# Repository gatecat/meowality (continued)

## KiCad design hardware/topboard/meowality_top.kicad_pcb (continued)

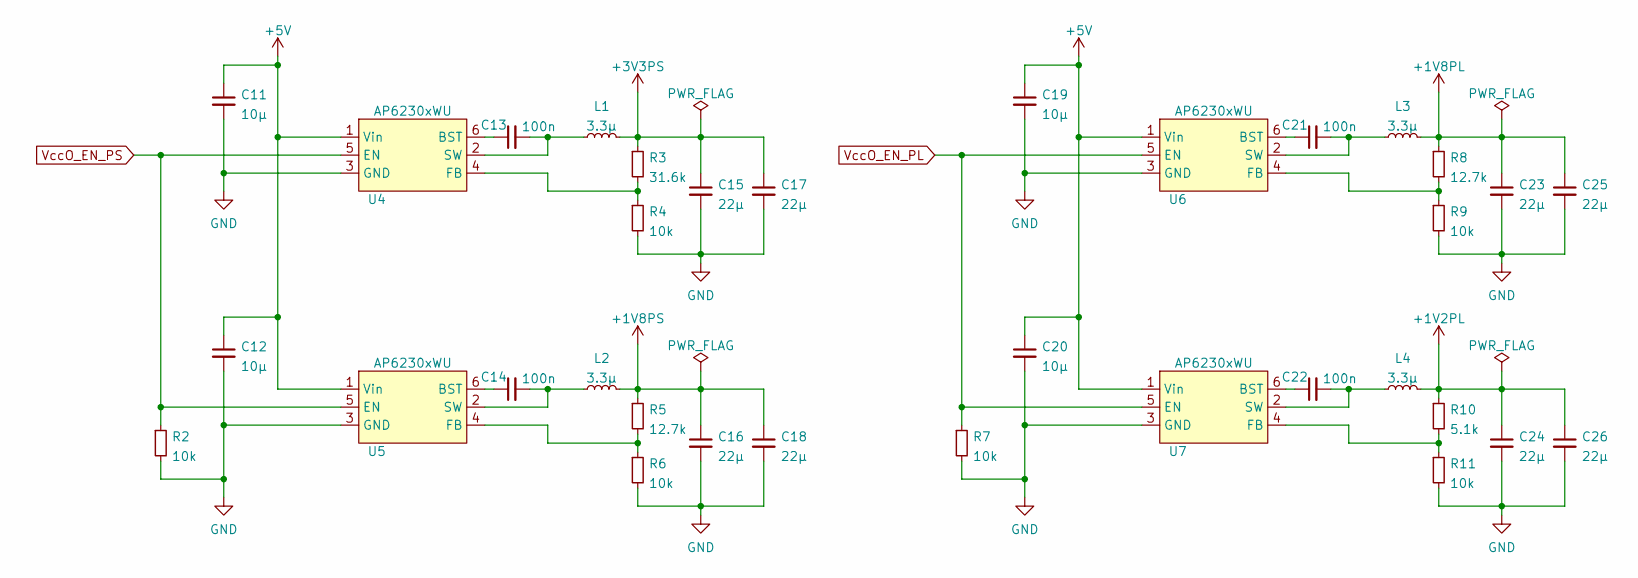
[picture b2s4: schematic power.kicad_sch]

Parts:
C11, C12, C19, C20: 10µ; C_0805_2012Metric
C13, C14, C21, C22: 100n; C_0402_1005Metric
C15, C16, C17, C18, C23, C24, C25, C26: 22µ; C_1206_3216Metric
L1, L2, L3, L4: 3.3µ; BWVS00606045
R2, R4, R6, R7, R9, R11: 10k; R_0402_1005Metric
R3: 31.6k; R_0402_1005Metric
R5, R8: 12.7k; R_0402_1005Metric
R10: 5.1k; R_0402_1005Metric
U4, U5, U6, U7: AP6230xWU; TSOT-23-6

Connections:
+1V2PL: C24.1, C26.1, L4.2, R10.1; also elsewhere on the board
+1V8PL: C23.1, C25.1, L3.2, R8.1; also elsewhere on the board
+1V8PS: C16.1, C18.1, L2.2, R5.1; also elsewhere on the board
+3V3PS: C15.1, C17.1, L1.2, R3.1; also elsewhere on the board
+5V: C11.1, C12.1, C19.1, C20.1, U4.1 (Vin), U5.1 (Vin), U6.1 (Vin), U7.1 (Vin); also elsewhere on the board
GND: C11.2, C12.2, C15.2, C16.2, C17.2, C18.2, C19.2, C20.2, C23.2, C24.2, C25.2, C26.2, R2.2, R4.2, R6.2, R7.2, R9.2, R11.2, U4.3 (GND), U5.3 (GND), U6.3 (GND), U7.3 (GND); also elsewhere on the board
unnamed: C13.1, U4.6 (BST)
unnamed: C13.2, L1.1, U4.2 (SW)
unnamed: C14.1, U5.6 (BST)
unnamed: C14.2, L2.1, U5.2 (SW)
unnamed: C21.1, U6.6 (BST)
unnamed: C21.2, L3.1, U6.2 (SW)
unnamed: C22.1, U7.6 (BST)
unnamed: C22.2, L4.1, U7.2 (SW)
unnamed: R3.2, R4.1, U4.4 (FB)
unnamed: R5.2, R6.1, U5.4 (FB)
unnamed: R8.2, R9.1, U6.4 (FB)
unnamed: R10.2, R11.1, U7.4 (FB)
VccO_EN_PL: R7.1, U6.5 (EN), U7.5 (EN); also elsewhere on the board
VccO_EN_PS: R2.1, U4.5 (EN), U5.5 (EN); also elsewhere on the board

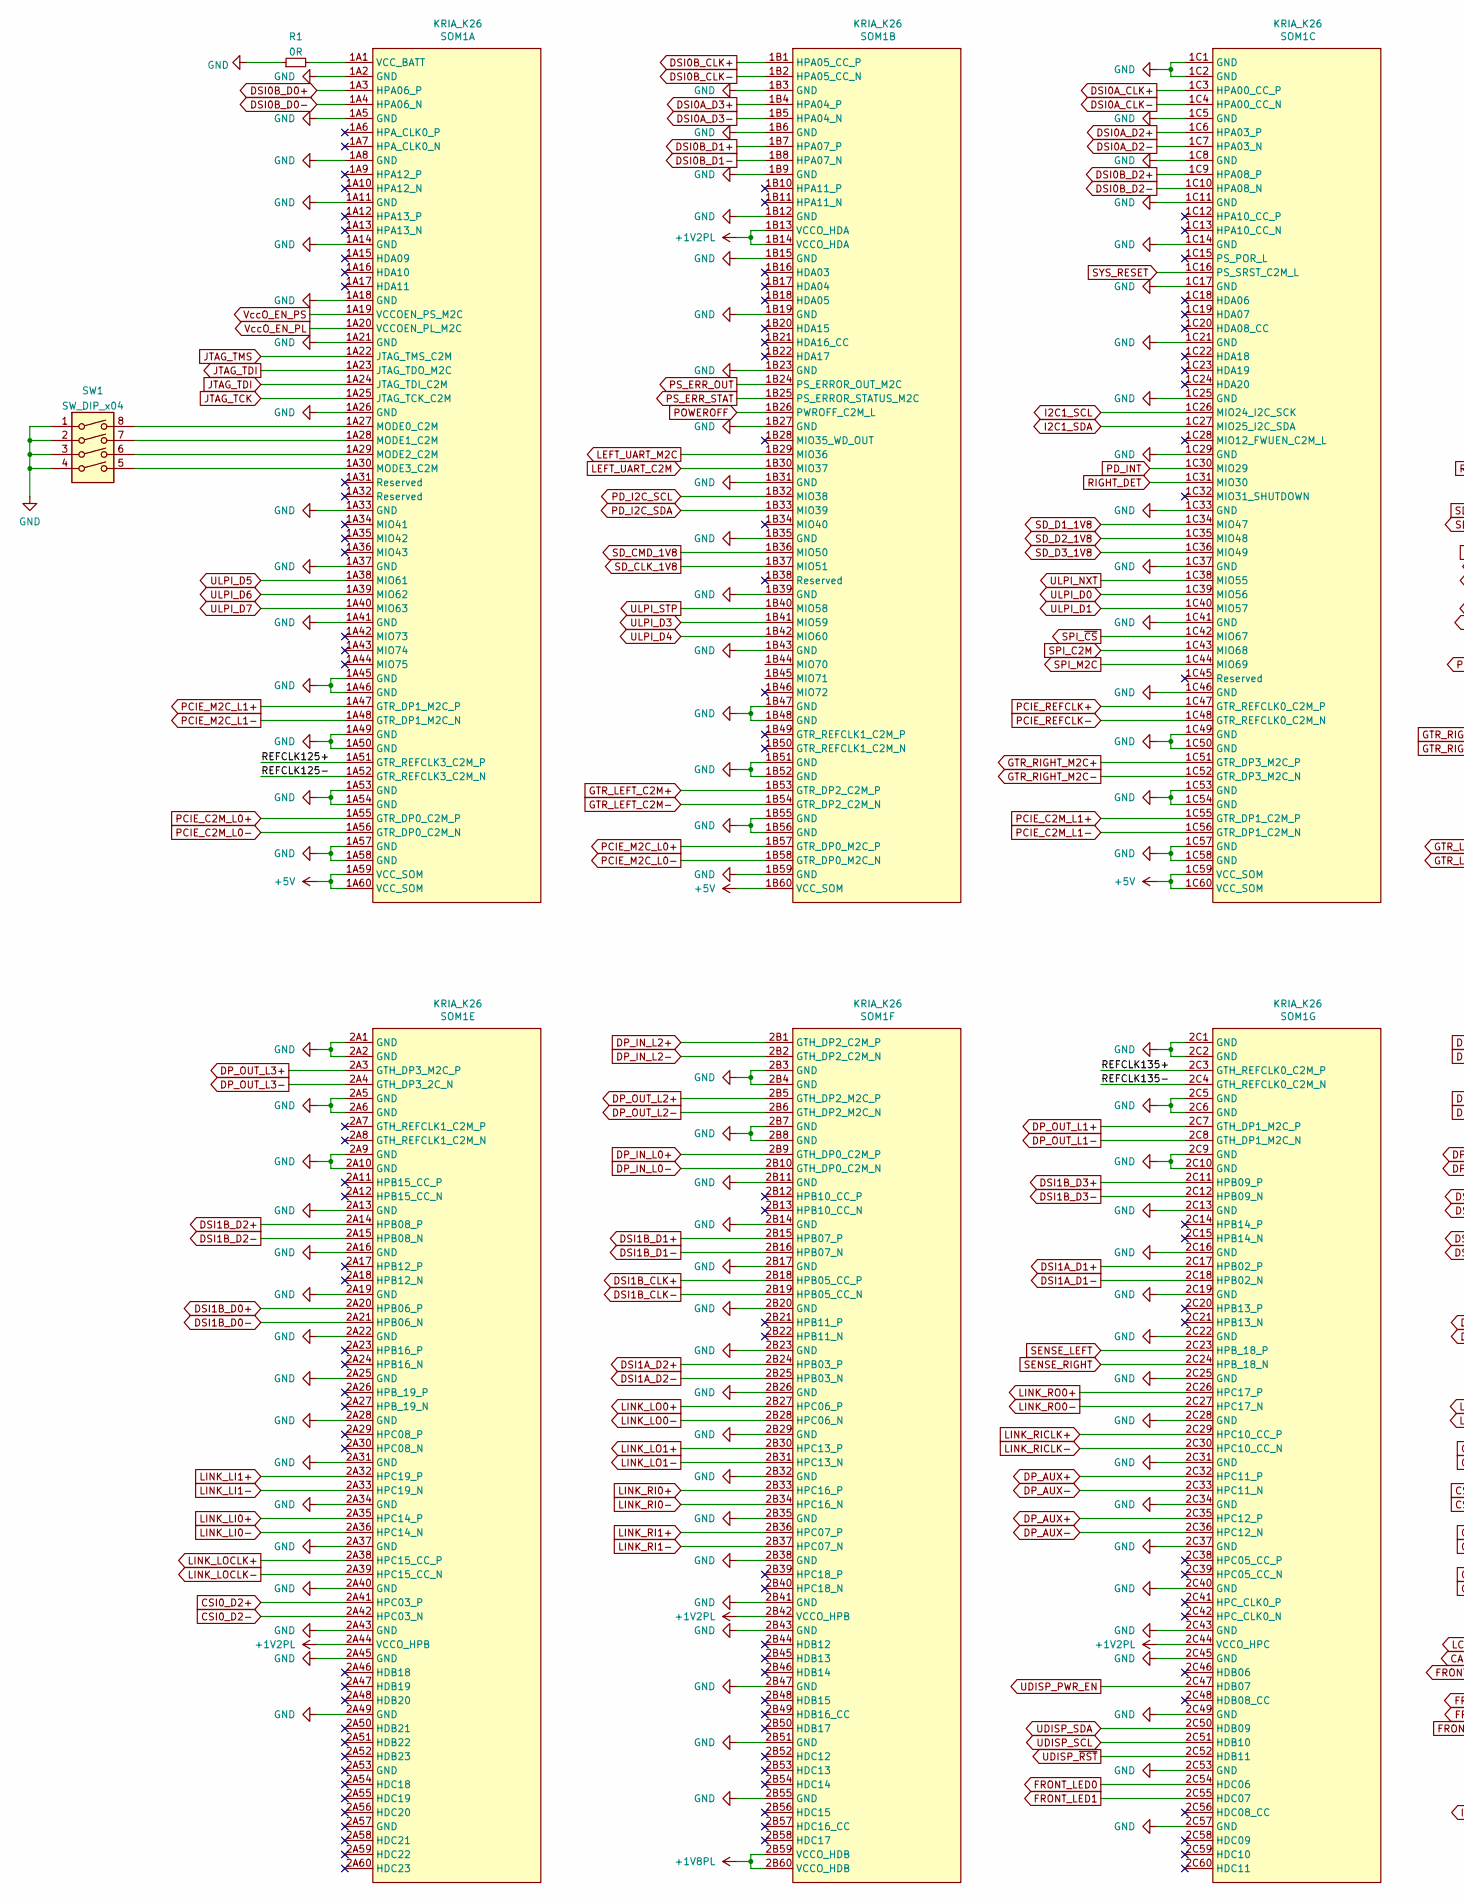
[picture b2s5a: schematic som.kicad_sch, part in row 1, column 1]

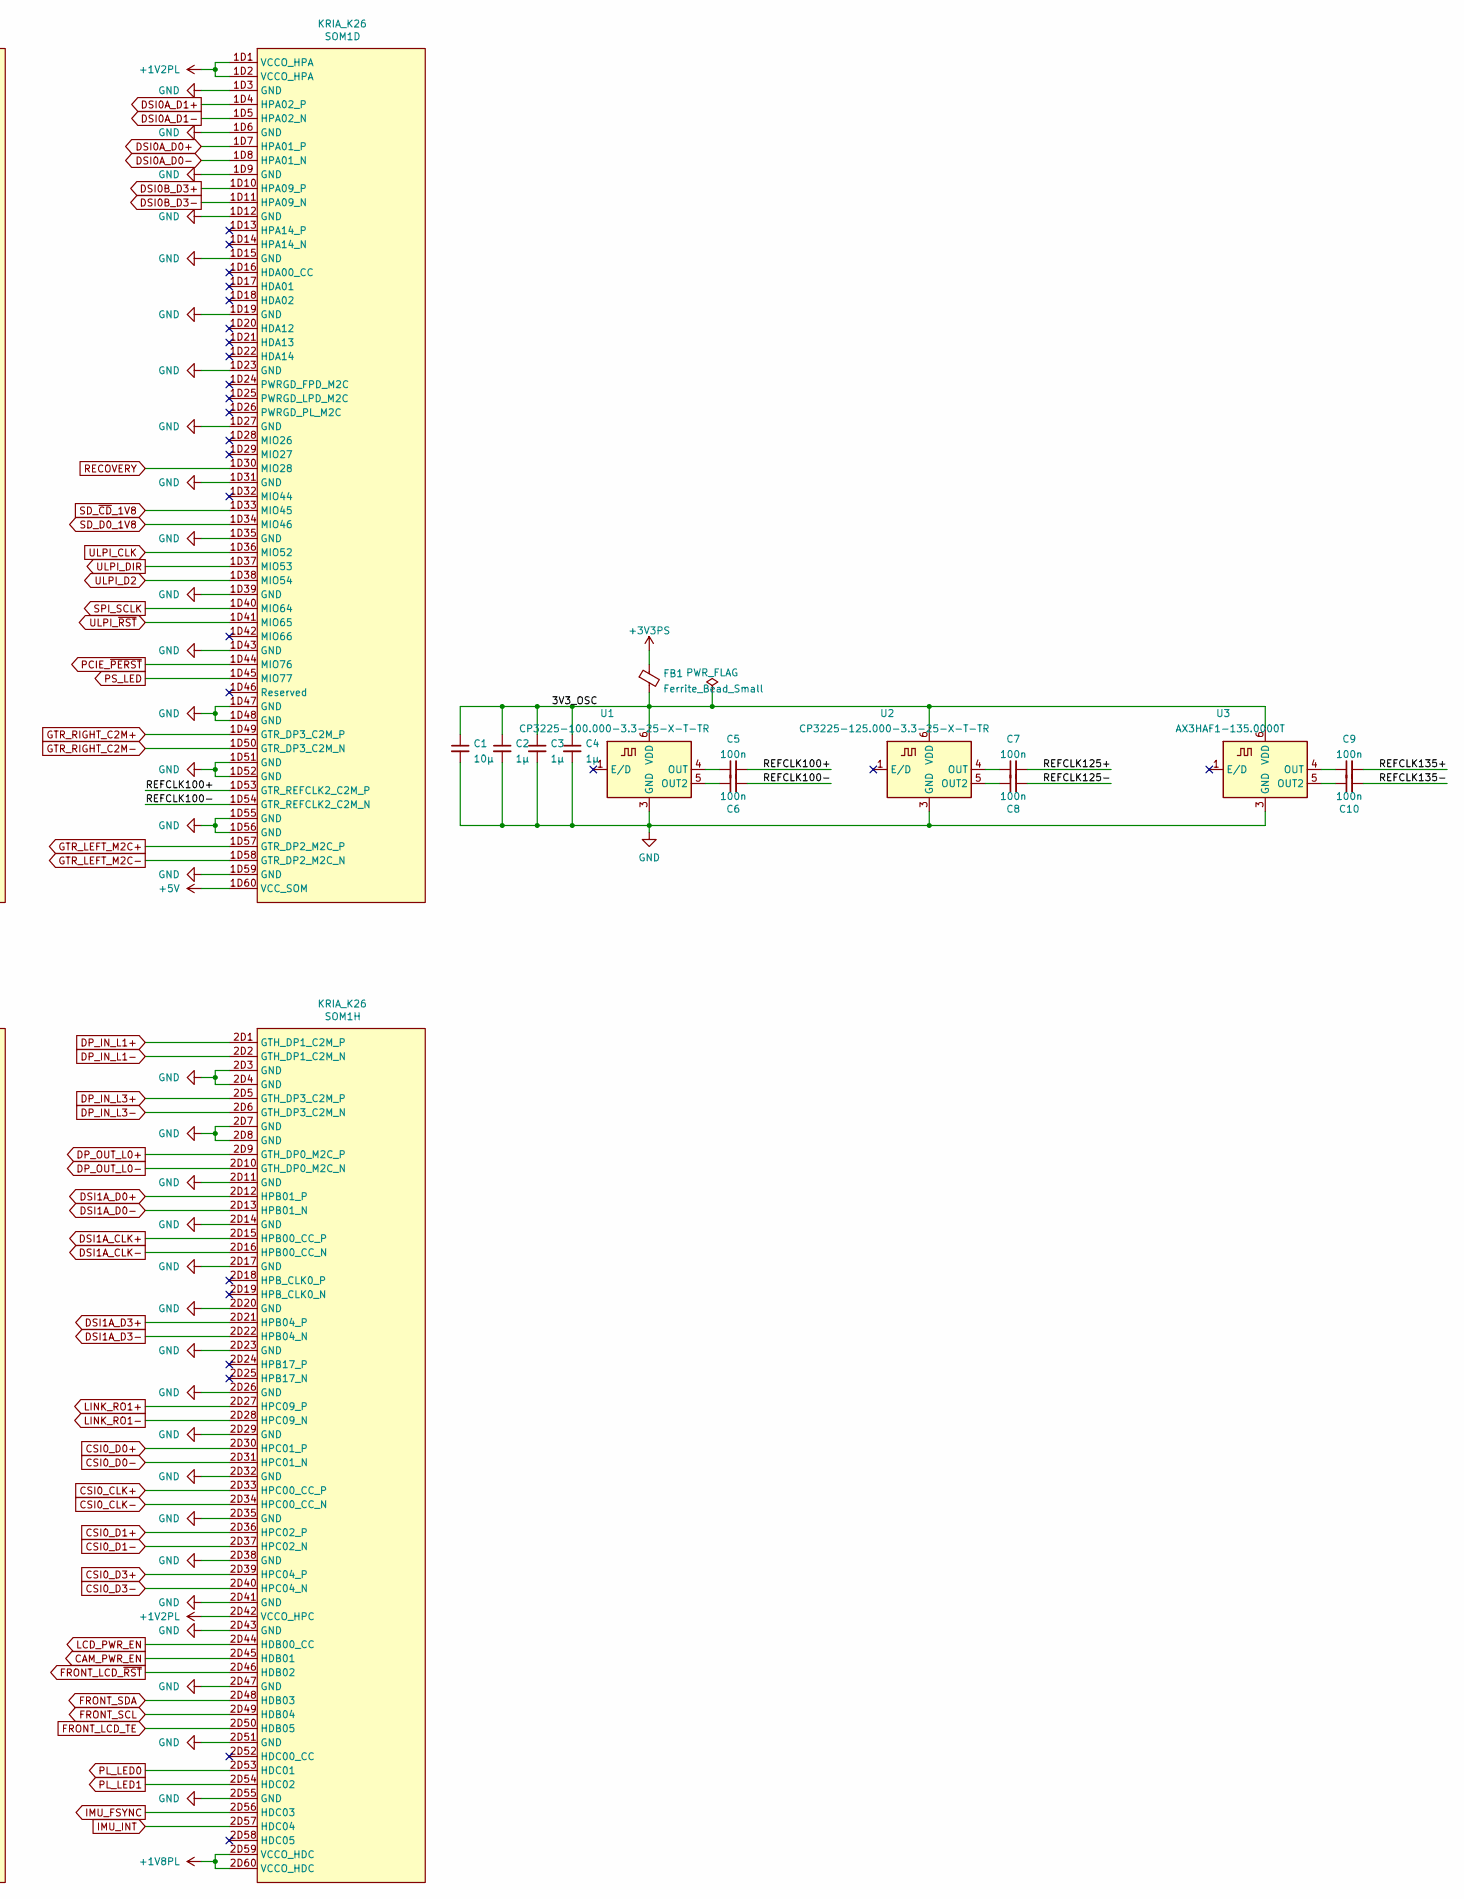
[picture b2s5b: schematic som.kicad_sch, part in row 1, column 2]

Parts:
C1: 10µ; C_0805_2012Metric
C2, C3, C4: 1µ; C_0603_1608Metric
C5, C6, C7, C8, C9, C10: 100n; C_0402_1005Metric
FB1: Ferrite_Bead_Small; L_0603_1608Metric
R1: 0R; R_0402_1005Metric
SOM1: KRIA_K26
SW1: SW_DIP_x04; SW_DIP_SPSTx04_Slide_Copal_CHS-04B_W7.62mm_P1.27mm
U1: CP3225-100.000-3.3-25-X-T-TR; Oscillator_SMD_IDT_JS6-6_5.0x3.2mm_P1.27mm
U2: CP3225-125.000-3.3-25-X-T-TR; Oscillator_SMD_IDT_JS6-6_5.0x3.2mm_P1.27mm
U3: AX3HAF1-135.0000T; Oscillator_SMD_IDT_JS6-6_5.0x3.2mm_P1.27mm

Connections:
+1V2PL: SOM1.1B13 (VCCO_HDA), SOM1.1B14 (VCCO_HDA), SOM1.1D1 (VCCO_HPA), SOM1.1D2 (VCCO_HPA), SOM1.2A44 (VCCO_HPB), SOM1.2B42 (VCCO_HPB), SOM1.2C44 (VCCO_HPC), SOM1.2D42 (VCCO_HPC); also elsewhere on the board
+1V8PL: SOM1.2B59 (VCCO_HDB), SOM1.2B60 (VCCO_HDB), SOM1.2D59 (VCCO_HDC), SOM1.2D60 (VCCO_HDC); also elsewhere on the board
+3V3PS: FB1.1; also elsewhere on the board
+5V: SOM1.1A59 (VCC_SOM), SOM1.1A60 (VCC_SOM), SOM1.1B60 (VCC_SOM), SOM1.1C59 (VCC_SOM), SOM1.1C60 (VCC_SOM), SOM1.1D60 (VCC_SOM); also elsewhere on the board
/SOM/3V3_OSC: C1.1, C2.1, C3.1, C4.1, FB1.2, U1.6 (VDD), U2.6 (VDD), U3.6 (VDD)
/SOM/REFCLK100+: C5.2, SOM1.1D53 (GTR_REFCLK2_C2M_P)
/SOM/REFCLK100-: C6.2, SOM1.1D54 (GTR_REFCLK2_C2M_N)
/SOM/REFCLK125+: C7.2, SOM1.1A51 (GTR_REFCLK3_C2M_P)
/SOM/REFCLK125-: C8.2, SOM1.1A52 (GTR_REFCLK3_C2M_N)
/SOM/REFCLK135+: C9.2, SOM1.2C3 (GTH_REFCLK0_C2M_P)
/SOM/REFCLK135-: C10.2, SOM1.2C4 (GTH_REFCLK0_C2M_N)
CAM_PWR_EN: SOM1.2D45 (HDB01); also elsewhere on the board
CSI0_CLK+: SOM1.2D33 (HPC00_CC_P); also elsewhere on the board
CSI0_CLK-: SOM1.2D34 (HPC00_CC_N); also elsewhere on the board
CSI0_D0+: SOM1.2D30 (HPC01_P); also elsewhere on the board
CSI0_D0-: SOM1.2D31 (HPC01_N); also elsewhere on the board
CSI0_D1+: SOM1.2D36 (HPC02_P); also elsewhere on the board
CSI0_D1-: SOM1.2D37 (HPC02_N); also elsewhere on the board
CSI0_D2+: SOM1.2A41 (HPC03_P); also elsewhere on the board
CSI0_D2-: SOM1.2A42 (HPC03_N); also elsewhere on the board
CSI0_D3+: SOM1.2D39 (HPC04_P); also elsewhere on the board
CSI0_D3-: SOM1.2D40 (HPC04_N); also elsewhere on the board
DP_AUX+: SOM1.2C32 (HPC11_P), SOM1.2C35 (HPC12_P); also elsewhere on the board
DP_AUX-: SOM1.2C33 (HPC11_N), SOM1.2C36 (HPC12_N); also elsewhere on the board
DP_IN_L0+: SOM1.2B9 (GTH_DP0_C2M_P); also elsewhere on the board
DP_IN_L0-: SOM1.2B10 (GTH_DP0_C2M_N); also elsewhere on the board
DP_IN_L1+: SOM1.2D1 (GTH_DP1_C2M_P); also elsewhere on the board
DP_IN_L1-: SOM1.2D2 (GTH_DP1_C2M_N); also elsewhere on the board
DP_IN_L2+: SOM1.2B1 (GTH_DP2_C2M_P); also elsewhere on the board
DP_IN_L2-: SOM1.2B2 (GTH_DP2_C2M_N); also elsewhere on the board
DP_IN_L3+: SOM1.2D5 (GTH_DP3_C2M_P); also elsewhere on the board
DP_IN_L3-: SOM1.2D6 (GTH_DP3_C2M_N); also elsewhere on the board
DP_OUT_L0+: SOM1.2D9 (GTH_DP0_M2C_P); also elsewhere on the board
DP_OUT_L0-: SOM1.2D10 (GTH_DP0_M2C_N); also elsewhere on the board
DP_OUT_L1+: SOM1.2C7 (GTH_DP1_M2C_P); also elsewhere on the board
DP_OUT_L1-: SOM1.2C8 (GTH_DP1_M2C_N); also elsewhere on the board
DP_OUT_L2+: SOM1.2B5 (GTH_DP2_M2C_P); also elsewhere on the board
DP_OUT_L2-: SOM1.2B6 (GTH_DP2_M2C_N); also elsewhere on the board
DP_OUT_L3+: SOM1.2A3 (GTH_DP3_M2C_P); also elsewhere on the board
DP_OUT_L3-: SOM1.2A4 (GTH_DP3_2C_N); also elsewhere on the board
DSI0A_CLK+: SOM1.1C3 (HPA00_CC_P); also elsewhere on the board
DSI0A_CLK-: SOM1.1C4 (HPA00_CC_N); also elsewhere on the board
DSI0A_D0+: SOM1.1D7 (HPA01_P); also elsewhere on the board
DSI0A_D0-: SOM1.1D8 (HPA01_N); also elsewhere on the board
DSI0A_D1+: SOM1.1D4 (HPA02_P); also elsewhere on the board
DSI0A_D1-: SOM1.1D5 (HPA02_N); also elsewhere on the board
DSI0A_D2+: SOM1.1C6 (HPA03_P); also elsewhere on the board
DSI0A_D2-: SOM1.1C7 (HPA03_N); also elsewhere on the board
DSI0A_D3+: SOM1.1B4 (HPA04_P); also elsewhere on the board
DSI0A_D3-: SOM1.1B5 (HPA04_N); also elsewhere on the board
DSI0B_CLK+: SOM1.1B1 (HPA05_CC_P); also elsewhere on the board
DSI0B_CLK-: SOM1.1B2 (HPA05_CC_N); also elsewhere on the board
DSI0B_D0+: SOM1.1A3 (HPA06_P); also elsewhere on the board
DSI0B_D0-: SOM1.1A4 (HPA06_N); also elsewhere on the board
DSI0B_D1+: SOM1.1B7 (HPA07_P); also elsewhere on the board
DSI0B_D1-: SOM1.1B8 (HPA07_N); also elsewhere on the board
DSI0B_D2+: SOM1.1C9 (HPA08_P); also elsewhere on the board
DSI0B_D2-: SOM1.1C10 (HPA08_N); also elsewhere on the board
DSI0B_D3+: SOM1.1D10 (HPA09_P); also elsewhere on the board
DSI0B_D3-: SOM1.1D11 (HPA09_N); also elsewhere on the board
DSI1A_CLK+: SOM1.2D15 (HPB00_CC_P); also elsewhere on the board
DSI1A_CLK-: SOM1.2D16 (HPB00_CC_N); also elsewhere on the board
DSI1A_D0+: SOM1.2D12 (HPB01_P); also elsewhere on the board
DSI1A_D0-: SOM1.2D13 (HPB01_N); also elsewhere on the board
DSI1A_D1+: SOM1.2C17 (HPB02_P); also elsewhere on the board
DSI1A_D1-: SOM1.2C18 (HPB02_N); also elsewhere on the board
DSI1A_D2+: SOM1.2B24 (HPB03_P); also elsewhere on the board
DSI1A_D2-: SOM1.2B25 (HPB03_N); also elsewhere on the board
DSI1A_D3+: SOM1.2D21 (HPB04_P); also elsewhere on the board
DSI1A_D3-: SOM1.2D22 (HPB04_N); also elsewhere on the board
DSI1B_CLK+: SOM1.2B18 (HPB05_CC_P); also elsewhere on the board
DSI1B_CLK-: SOM1.2B19 (HPB05_CC_N); also elsewhere on the board
DSI1B_D0+: SOM1.2A20 (HPB06_P); also elsewhere on the board
DSI1B_D0-: SOM1.2A21 (HPB06_N); also elsewhere on the board
DSI1B_D1+: SOM1.2B15 (HPB07_P); also elsewhere on the board
DSI1B_D1-: SOM1.2B16 (HPB07_N); also elsewhere on the board
DSI1B_D2+: SOM1.2A14 (HPB08_P); also elsewhere on the board
DSI1B_D2-: SOM1.2A15 (HPB08_N); also elsewhere on the board
DSI1B_D3+: SOM1.2C11 (HPB09_P); also elsewhere on the board
DSI1B_D3-: SOM1.2C12 (HPB09_N); also elsewhere on the board
FRONT_LCD_TE: SOM1.2D50 (HDB05); also elsewhere on the board
FRONT_LCD_~RST: SOM1.2D46 (HDB02); also elsewhere on the board
FRONT_LED0: SOM1.2C54 (HDC06); also elsewhere on the board
FRONT_LED1: SOM1.2C55 (HDC07); also elsewhere on the board
FRONT_SCL: SOM1.2D49 (HDB04); also elsewhere on the board
FRONT_SDA: SOM1.2D48 (HDB03); also elsewhere on the board
GND: C1.2, C2.2, C3.2, C4.2, R1.1, SOM1.1A2 (GND), SOM1.1A5 (GND), SOM1.1A8 (GND), SOM1.1A11 (GND), SOM1.1A14 (GND), SOM1.1A18 (GND), SOM1.1A21 (GND), SOM1.1A26 (GND), SOM1.1A33 (GND), SOM1.1A37 (GND), SOM1.1A41 (GND), SOM1.1A45 (GND), SOM1.1A46 (GND), SOM1.1A49 (GND), SOM1.1A50 (GND), SOM1.1A53 (GND), SOM1.1A54 (GND), SOM1.1A57 (GND), SOM1.1A58 (GND), SOM1.1B3 (GND), SOM1.1B6 (GND), SOM1.1B9 (GND), SOM1.1B12 (GND), SOM1.1B15 (GND), SOM1.1B19 (GND), SOM1.1B23 (GND), SOM1.1B27 (GND), SOM1.1B31 (GND), SOM1.1B35 (GND), SOM1.1B39 (GND), SOM1.1B43 (GND), SOM1.1B47 (GND), SOM1.1B48 (GND), SOM1.1B51 (GND), SOM1.1B52 (GND), SOM1.1B55 (GND), SOM1.1B56 (GND), SOM1.1B59 (GND), SOM1.1C1 (GND), SOM1.1C2 (GND), SOM1.1C5 (GND), SOM1.1C8 (GND), SOM1.1C11 (GND), SOM1.1C14 (GND), SOM1.1C17 (GND), SOM1.1C21 (GND), SOM1.1C25 (GND), SOM1.1C29 (GND), SOM1.1C33 (GND), SOM1.1C37 (GND), SOM1.1C41 (GND), SOM1.1C46 (GND), SOM1.1C49 (GND), SOM1.1C50 (GND), SOM1.1C53 (GND), SOM1.1C54 (GND), SOM1.1C57 (GND), SOM1.1C58 (GND), SOM1.1D3 (GND), SOM1.1D6 (GND), SOM1.1D9 (GND), SOM1.1D12 (GND), SOM1.1D15 (GND), SOM1.1D19 (GND), SOM1.1D23 (GND), SOM1.1D27 (GND), SOM1.1D31 (GND), SOM1.1D35 (GND), SOM1.1D39 (GND), SOM1.1D43 (GND), SOM1.1D47 (GND), SOM1.1D48 (GND), SOM1.1D51 (GND), SOM1.1D52 (GND), SOM1.1D55 (GND), SOM1.1D56 (GND), SOM1.1D59 (GND), SOM1.2A1 (GND), SOM1.2A2 (GND), SOM1.2A5 (GND), SOM1.2A6 (GND), SOM1.2A9 (GND), SOM1.2A10 (GND), SOM1.2A13 (GND), SOM1.2A16 (GND), SOM1.2A19 (GND), SOM1.2A22 (GND), SOM1.2A25 (GND), SOM1.2A28 (GND), SOM1.2A31 (GND), SOM1.2A34 (GND), SOM1.2A37 (GND), SOM1.2A40 (GND), SOM1.2A43 (GND), SOM1.2A45 (GND), SOM1.2A49 (GND), SOM1.2B3 (GND), SOM1.2B4 (GND), SOM1.2B7 (GND), SOM1.2B8 (GND), SOM1.2B11 (GND), SOM1.2B14 (GND), SOM1.2B17 (GND), SOM1.2B20 (GND), SOM1.2B23 (GND), SOM1.2B26 (GND), SOM1.2B29 (GND), SOM1.2B32 (GND), SOM1.2B35 (GND), SOM1.2B38 (GND), SOM1.2B41 (GND), SOM1.2B43 (GND), SOM1.2B47 (GND), SOM1.2B51 (GND), SOM1.2B55 (GND), SOM1.2C1 (GND), SOM1.2C2 (GND), SOM1.2C5 (GND), SOM1.2C6 (GND), SOM1.2C9 (GND), SOM1.2C10 (GND), SOM1.2C13 (GND), SOM1.2C16 (GND), SOM1.2C19 (GND), SOM1.2C22 (GND), SOM1.2C25 (GND), SOM1.2C28 (GND), SOM1.2C31 (GND), SOM1.2C34 (GND), SOM1.2C37 (GND), SOM1.2C40 (GND), SOM1.2C43 (GND), SOM1.2C45 (GND), SOM1.2C49 (GND), SOM1.2C53 (GND), SOM1.2C57 (GND), SOM1.2D3 (GND), SOM1.2D4 (GND), SOM1.2D7 (GND), SOM1.2D8 (GND), SOM1.2D11 (GND), SOM1.2D14 (GND), SOM1.2D17 (GND), SOM1.2D20 (GND), SOM1.2D23 (GND), SOM1.2D26 (GND), SOM1.2D29 (GND), SOM1.2D32 (GND), SOM1.2D35 (GND), SOM1.2D38 (GND), SOM1.2D41 (GND), SOM1.2D43 (GND), SOM1.2D47 (GND), SOM1.2D51 (GND), SOM1.2D55 (GND), SW1.1, SW1.2, SW1.3, SW1.4, U1.3 (GND), U2.3 (GND), U3.3 (GND); also elsewhere on the board
GTR_LEFT_C2M+: SOM1.1B53 (GTR_DP2_C2M_P); also elsewhere on the board
GTR_LEFT_C2M-: SOM1.1B54 (GTR_DP2_C2M_N); also elsewhere on the board
GTR_LEFT_M2C+: SOM1.1D57 (GTR_DP2_M2C_P); also elsewhere on the board
GTR_LEFT_M2C-: SOM1.1D58 (GTR_DP2_M2C_N); also elsewhere on the board
GTR_RIGHT_C2M+: SOM1.1D49 (GTR_DP3_C2M_P); also elsewhere on the board
GTR_RIGHT_C2M-: SOM1.1D50 (GTR_DP3_C2M_N); also elsewhere on the board
GTR_RIGHT_M2C+: SOM1.1C51 (GTR_DP3_M2C_P); also elsewhere on the board
GTR_RIGHT_M2C-: SOM1.1C52 (GTR_DP3_M2C_N); also elsewhere on the board
I2C1_SCL: SOM1.1C26 (MIO24_I2C_SCK); also elsewhere on the board
I2C1_SDA: SOM1.1C27 (MIO25_I2C_SDA); also elsewhere on the board
IMU_FSYNC: SOM1.2D56 (HDC03)
IMU_INT: SOM1.2D57 (HDC04); also elsewhere on the board
JTAG_TCK: SOM1.1A25 (JTAG_TCK_C2M); also elsewhere on the board
JTAG_TDI: SOM1.1A23 (JTAG_TDO_M2C), SOM1.1A24 (JTAG_TDI_C2M); also elsewhere on the board
JTAG_TMS: SOM1.1A22 (JTAG_TMS_C2M); also elsewhere on the board
LCD_PWR_EN: SOM1.2D44 (HDB00_CC); also elsewhere on the board
LEFT_UART_C2M: SOM1.1B30 (MIO37); also elsewhere on the board
LEFT_UART_M2C: SOM1.1B29 (MIO36); also elsewhere on the board
LINK_LI0+: SOM1.2A35 (HPC14_P); also elsewhere on the board
LINK_LI0-: SOM1.2A36 (HPC14_N); also elsewhere on the board
LINK_LI1+: SOM1.2A32 (HPC19_P); also elsewhere on the board
LINK_LI1-: SOM1.2A33 (HPC19_N); also elsewhere on the board
LINK_LO0+: SOM1.2B27 (HPC06_P); also elsewhere on the board
LINK_LO0-: SOM1.2B28 (HPC06_N); also elsewhere on the board
LINK_LO1+: SOM1.2B30 (HPC13_P); also elsewhere on the board
LINK_LO1-: SOM1.2B31 (HPC13_N); also elsewhere on the board
LINK_LOCLK+: SOM1.2A38 (HPC15_CC_P); also elsewhere on the board
LINK_LOCLK-: SOM1.2A39 (HPC15_CC_N); also elsewhere on the board
LINK_RI0+: SOM1.2B33 (HPC16_P); also elsewhere on the board
LINK_RI0-: SOM1.2B34 (HPC16_N); also elsewhere on the board
LINK_RI1+: SOM1.2B36 (HPC07_P); also elsewhere on the board
LINK_RI1-: SOM1.2B37 (HPC07_N); also elsewhere on the board
LINK_RICLK+: SOM1.2C29 (HPC10_CC_P); also elsewhere on the board
LINK_RICLK-: SOM1.2C30 (HPC10_CC_N); also elsewhere on the board
LINK_RO0+: SOM1.2C26 (HPC17_P); also elsewhere on the board
LINK_RO0-: SOM1.2C27 (HPC17_N); also elsewhere on the board
LINK_RO1+: SOM1.2D27 (HPC09_P); also elsewhere on the board
LINK_RO1-: SOM1.2D28 (HPC09_N); also elsewhere on the board
unnamed: C5.1, U1.4 (OUT)
unnamed: C6.1, U1.5 (OUT2)
unnamed: C7.1, U2.4 (OUT)
unnamed: C8.1, U2.5 (OUT2)
unnamed: C9.1, U3.4 (OUT)
unnamed: C10.1, U3.5 (OUT2)
unnamed: R1.2, SOM1.1A1 (VCC_BATT)
unnamed: SOM1.1A27 (MODE0_C2M), SW1.8
unnamed: SOM1.1A28 (MODE1_C2M), SW1.7
unnamed: SOM1.1A29 (MODE2_C2M), SW1.6
unnamed: SOM1.1A30 (MODE3_C2M), SW1.5
PCIE_C2M_L0+: SOM1.1A55 (GTR_DP0_C2M_P); also elsewhere on the board
PCIE_C2M_L0-: SOM1.1A56 (GTR_DP0_C2M_N); also elsewhere on the board
PCIE_C2M_L1+: SOM1.1C55 (GTR_DP1_C2M_P); also elsewhere on the board
PCIE_C2M_L1-: SOM1.1C56 (GTR_DP1_C2M_N); also elsewhere on the board
PCIE_M2C_L0+: SOM1.1B57 (GTR_DP0_M2C_P); also elsewhere on the board
PCIE_M2C_L0-: SOM1.1B58 (GTR_DP0_M2C_N); also elsewhere on the board
PCIE_M2C_L1+: SOM1.1A47 (GTR_DP1_M2C_P); also elsewhere on the board
PCIE_M2C_L1-: SOM1.1A48 (GTR_DP1_M2C_N); also elsewhere on the board
PCIE_REFCLK+: SOM1.1C47 (GTR_REFCLK0_C2M_P); also elsewhere on the board
PCIE_REFCLK-: SOM1.1C48 (GTR_REFCLK0_C2M_N); also elsewhere on the board
PCIE_~PERST: SOM1.1D44 (MIO76); also elsewhere on the board
PD_I2C_SCL: SOM1.1B32 (MIO38); also elsewhere on the board
PD_I2C_SDA: SOM1.1B33 (MIO39); also elsewhere on the board
PD_INT: SOM1.1C30 (MIO29); also elsewhere on the board
PL_LED0: SOM1.2D53 (HDC01); also elsewhere on the board
PL_LED1: SOM1.2D54 (HDC02); also elsewhere on the board
POWEROFF: SOM1.1B26 (PWROFF_C2M_L); also elsewhere on the board
PS_ERR_OUT: SOM1.1B24 (PS_ERROR_OUT_M2C); also elsewhere on the board
PS_ERR_STAT: SOM1.1B25 (PS_ERROR_STATUS_M2C); also elsewhere on the board
PS_LED: SOM1.1D45 (MIO77); also elsewhere on the board
RECOVERY: SOM1.1D30 (MIO28); also elsewhere on the board
RIGHT_DET: SOM1.1C31 (MIO30); also elsewhere on the board
SD_CLK_1V8: SOM1.1B37 (MIO51); also elsewhere on the board
SD_CMD_1V8: SOM1.1B36 (MIO50); also elsewhere on the board
SD_D0_1V8: SOM1.1D34 (MIO46); also elsewhere on the board
SD_D1_1V8: SOM1.1C34 (MIO47); also elsewhere on the board
SD_D2_1V8: SOM1.1C35 (MIO48); also elsewhere on the board
SD_D3_1V8: SOM1.1C36 (MIO49); also elsewhere on the board
SD_~CD_1V8: SOM1.1D33 (MIO45); also elsewhere on the board
SENSE_LEFT: SOM1.2C23 (HPB_18_P); also elsewhere on the board
SENSE_RIGHT: SOM1.2C24 (HPB_18_N); also elsewhere on the board
SPI_C2M: SOM1.1C43 (MIO68)
SPI_M2C: SOM1.1C44 (MIO69)
SPI_SCLK: SOM1.1D40 (MIO64)
SPI_~CS: SOM1.1C42 (MIO67); also elsewhere on the board
SYS_RESET: SOM1.1C16 (PS_SRST_C2M_L); also elsewhere on the board
UDISP_PWR_EN: SOM1.2C47 (HDB07); also elsewhere on the board
UDISP_SCL: SOM1.2C51 (HDB10); also elsewhere on the board
UDISP_SDA: SOM1.2C50 (HDB09); also elsewhere on the board
UDISP_~RST: SOM1.2C52 (HDB11); also elsewhere on the board
ULPI_CLK: SOM1.1D36 (MIO52); also elsewhere on the board
ULPI_D0: SOM1.1C39 (MIO56); also elsewhere on the board
ULPI_D1: SOM1.1C40 (MIO57); also elsewhere on the board
ULPI_D2: SOM1.1D38 (MIO54); also elsewhere on the board
ULPI_D3: SOM1.1B41 (MIO59); also elsewhere on the board
ULPI_D4: SOM1.1B42 (MIO60); also elsewhere on the board
ULPI_D5: SOM1.1A38 (MIO61); also elsewhere on the board
ULPI_D6: SOM1.1A39 (MIO62); also elsewhere on the board
ULPI_D7: SOM1.1A40 (MIO63); also elsewhere on the board
ULPI_DIR: SOM1.1D37 (MIO53); also elsewhere on the board
ULPI_NXT: SOM1.1C38 (MIO55); also elsewhere on the board
ULPI_STP: SOM1.1B40 (MIO58); also elsewhere on the board
ULPI_~RST: SOM1.1D41 (MIO65); also elsewhere on the board
VccO_EN_PL: SOM1.1A20 (VCCOEN_PL_M2C); also elsewhere on the board
VccO_EN_PS: SOM1.1A19 (VCCOEN_PS_M2C); also elsewhere on the board

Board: 2 copper layers, 215 parts (1 on the bottom side), 308 nets, no tracks yet.
